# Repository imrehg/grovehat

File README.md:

# GroveHat for VIA VAB-820

[Grove][grove] break-out board for [VIA VAB-820](vab820).

Connectors:

 * 2 x I2C
 * 2 x Digital

[grove]: http://www.seeedstudio.com/wiki/Grove_System "Grove System"
[vab820]: http://www.viaembedded.com/en/boards/pico-itx/vab-820/ "VAB-820 product page"

## License

CERN Open Hardware License 1.2, see `LICENSE.txt`.

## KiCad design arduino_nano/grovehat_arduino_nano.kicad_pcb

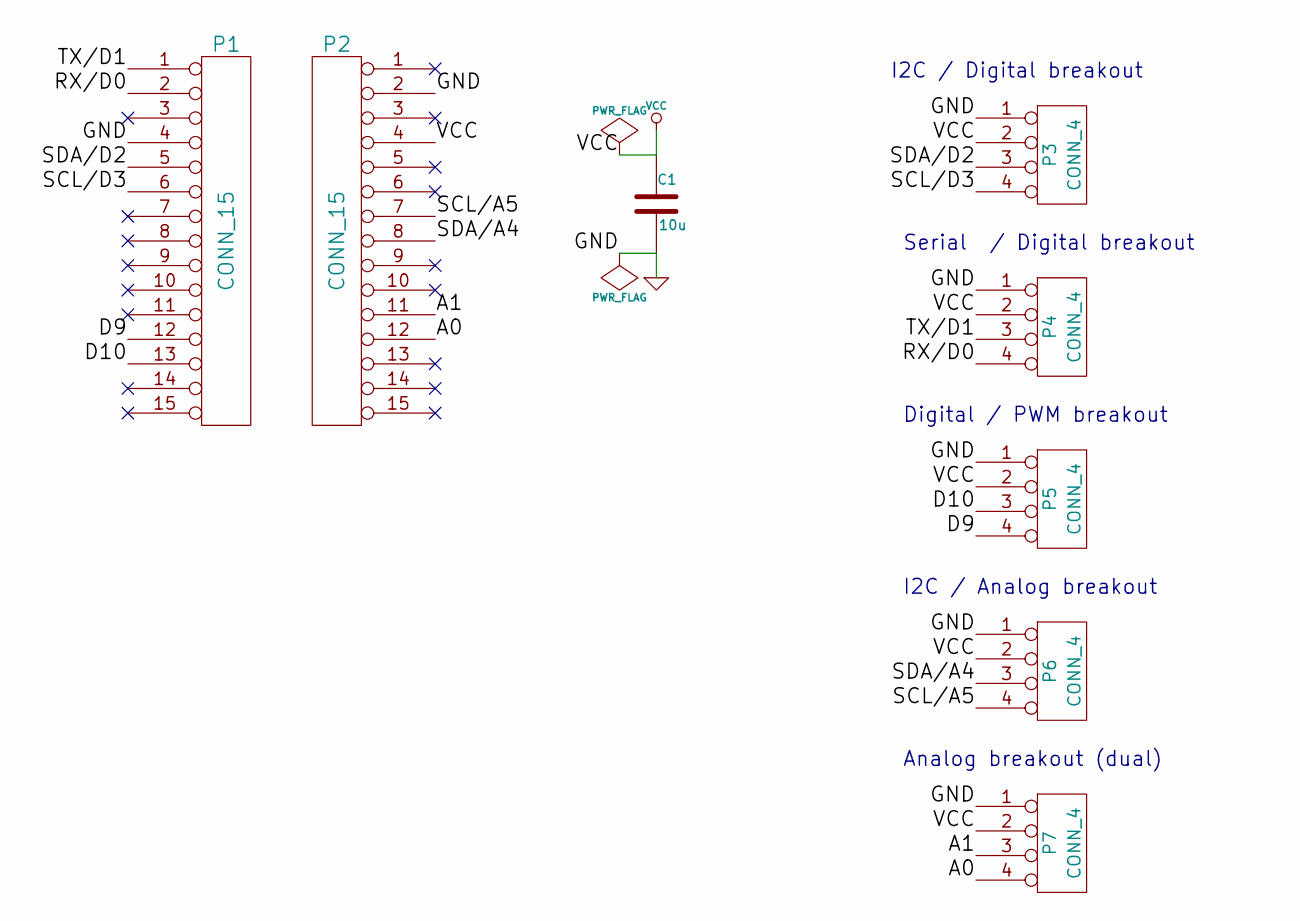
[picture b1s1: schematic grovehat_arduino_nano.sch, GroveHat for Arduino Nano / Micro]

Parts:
C1: 10u; SM0805
P1, P2: CONN_15
P3, P4, P6, P7: CONN_4; TWIG_2.0
P5: CONN_4

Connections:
/A0: P2.12, P7.4
/A1: P2.11, P7.3
/D9: P1.12, P5.4
/D10: P1.13, P5.3
/RX/D0: P1.2, P4.4
/SCL/A5: P2.7, P6.4
/SCL/D3: P1.6, P3.4
/SDA/A4: P2.8, P6.3
/SDA/D2: P1.5, P3.3
/TX/D1: P1.1, P4.3
GND: C1.2, P1.4, P2.2, P3.1, P4.1, P5.1, P6.1, P7.1
VCC: C1.1, P2.4, P3.2, P4.2, P5.2, P6.2, P7.2

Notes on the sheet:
I2C / Digital breakout
Serial / Digital breakout
Analog breakout (dual)
Digital / PWM breakout
I2C / Analog breakout

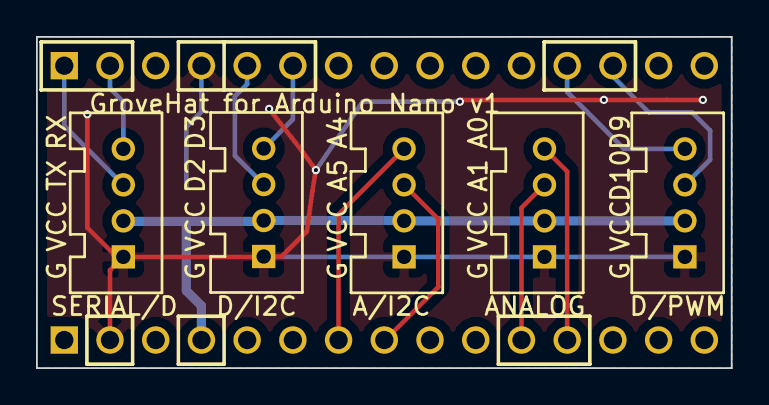
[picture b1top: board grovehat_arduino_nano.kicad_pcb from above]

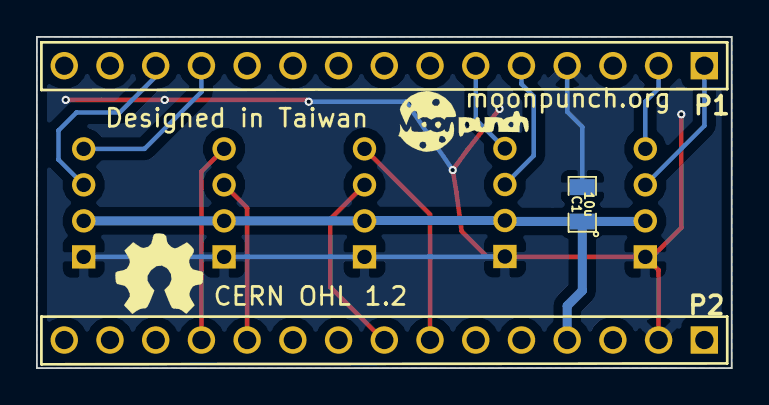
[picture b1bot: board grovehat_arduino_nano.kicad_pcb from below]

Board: 2 copper layers, 38.6 x 18.4 mm, 8 parts (3 on the bottom side), 12 nets.

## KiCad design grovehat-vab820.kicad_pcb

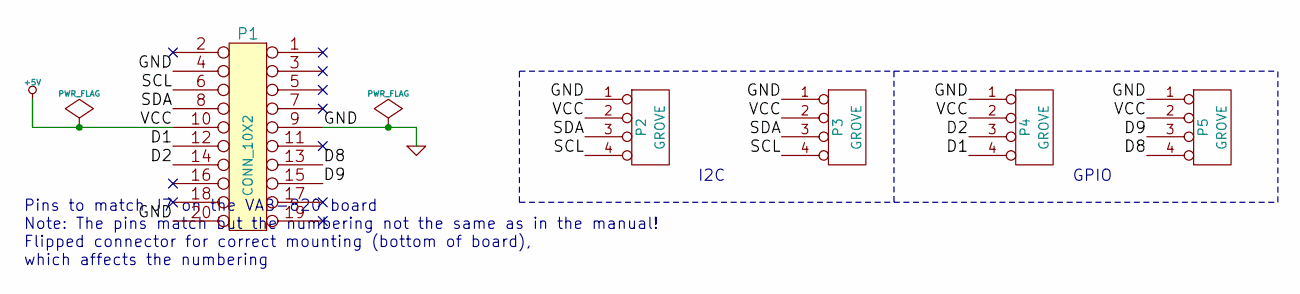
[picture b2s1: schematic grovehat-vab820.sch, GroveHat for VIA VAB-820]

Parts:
P1: CONN_10X2; pin_array_2mm_10x2
P2, P3, P4, P5: GROVE; TWIG_2.0

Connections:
+5V: P1.10, P2.2, P3.2, P4.2, P5.2
/D1: P1.12, P4.4
/D2: P1.14, P4.3
/D8: P1.13, P5.4
/D9: P1.15, P5.3
/SCL: P1.6, P2.4, P3.4
/SDA: P1.8, P2.3, P3.3
GND: P1.4, P1.9, P1.20, P2.1, P3.1, P4.1, P5.1

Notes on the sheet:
I2C
GPIO
Pins to match J7 on the VAB-820 board Note: The pins match but the numbering not the same as in the manual! Flipped connector for correct mounting (bottom of board), which affects the numbering

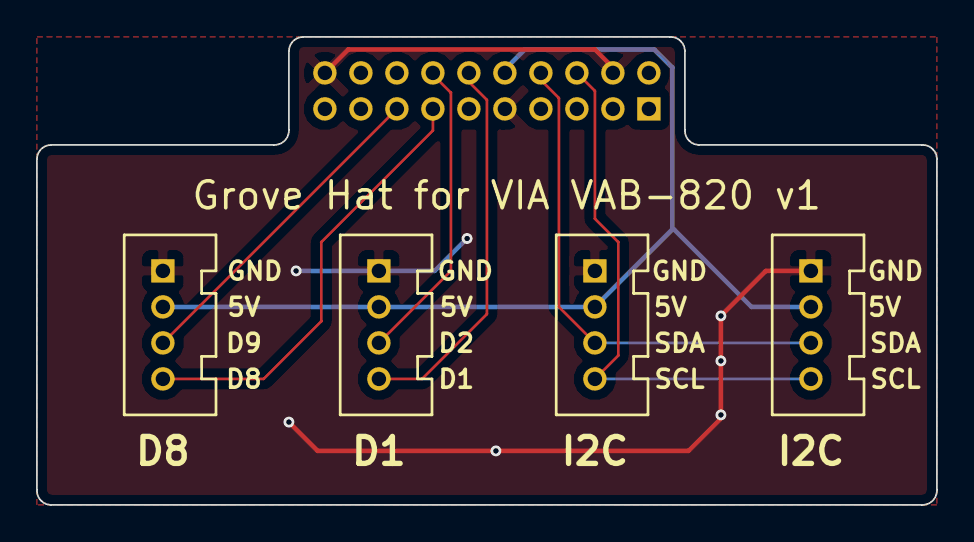
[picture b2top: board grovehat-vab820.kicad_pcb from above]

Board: 2 copper layers, 50.0 x 26.0 mm, 5 parts (1 on the bottom side), 8 nets.

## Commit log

2015-08-13 Schematic done
2015-08-15 first draft of GrooveHat
2015-08-15 adjust silkscreen
2015-08-16 updated PCB design, larger area, more spacious
2015-10-01 GroveHat for Arduino Nano v1
    As submitted for manufacturing.
2015-10-01 GroveHat for Arduino Nano v1 Gerber files
2015-10-01 nano: add part numbers to the schematics

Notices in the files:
arduino_nano/grovehat_arduino_nano.kicad_pcb:
CERN OHL 1.2
